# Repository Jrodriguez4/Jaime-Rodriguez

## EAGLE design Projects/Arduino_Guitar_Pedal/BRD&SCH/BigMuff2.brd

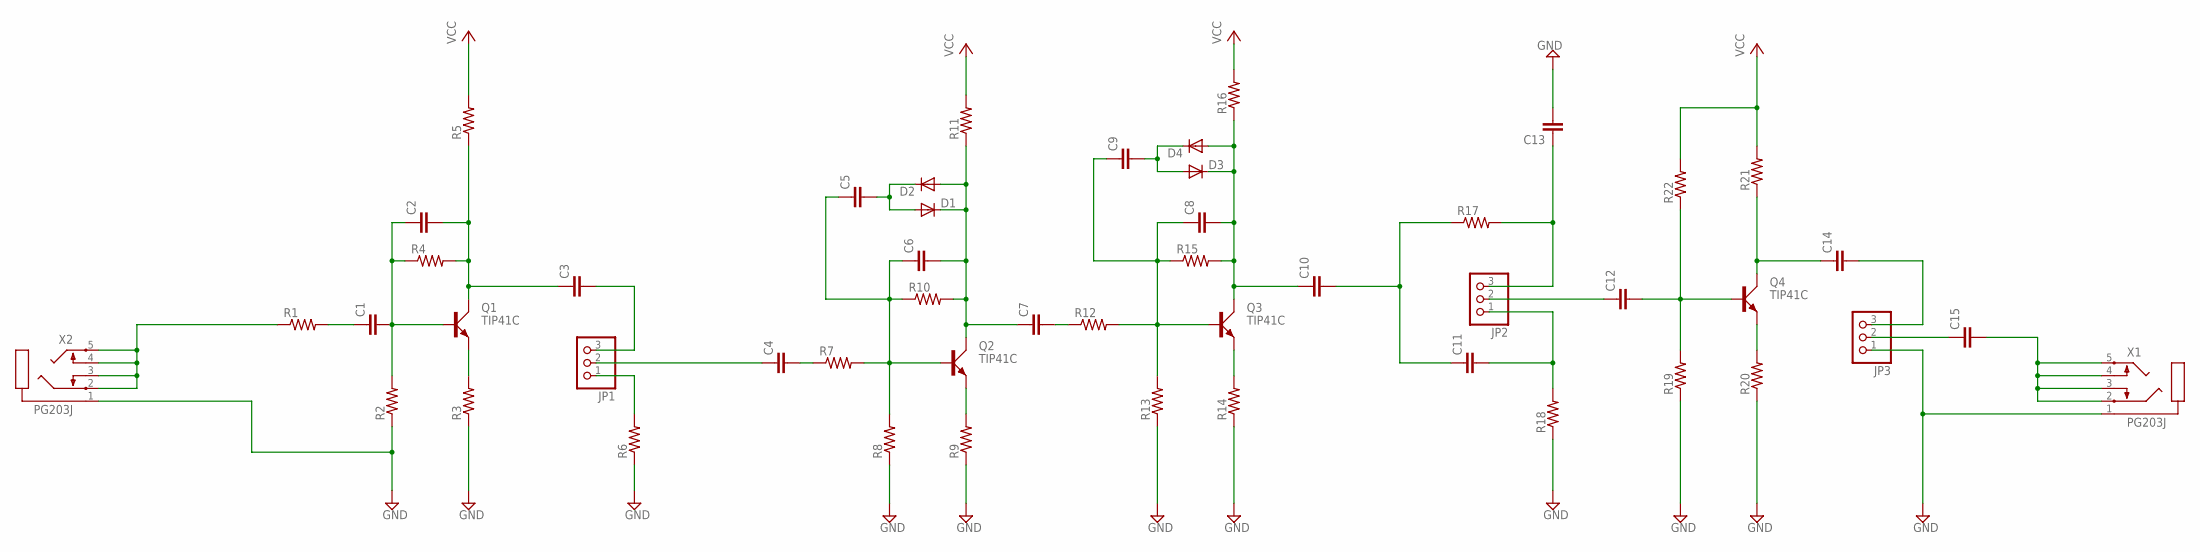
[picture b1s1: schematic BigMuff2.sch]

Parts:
C1, C2, C3, C4, C5, C6, C7, C8, C9, C10, C11, C12, C13, C14, C15: C2,5-3; C2.5-3
D1, D2, D3, D4: DIODE-D-2.5; D-2.5
JP1, JP2, JP3: PINHD-1X3; 1X03
Q1, Q2, Q3, Q4: TIP41C; TO220AV
R1, R2, R3, R4, R5, R6, R7, R8, R9, R10, R11, R12, R13, R14, R15, R16, R17, R18, R19, R20, R21, R22: R-US_0204/2V; 0204V
X1, X2: PG203J

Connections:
GND: C13.2, JP3.1, R2.1, R3.1, R6.1, R8.1, R9.1, R13.1, R14.1, R18.1, R19.1, R20.1, X1.1, X2.1; also elsewhere on the board
unnamed: C2.2, C3.1, Q1.C, R4.2, R5.1
unnamed: C1.2, C2.1, Q1.B, R2.2, R4.1
unnamed: C1.1, R1.2
unnamed: Q1.E, R3.2
unnamed: C3.2, JP1.3
unnamed: JP1.1, R6.2
unnamed: C14.1, Q4.C, R21.1
unnamed: C4.1, JP1.2
unnamed: C6.2, C7.1, D1.C, D2.A, Q2.C, R10.2, R11.1
unnamed: C5.2, D1.A, D2.C
unnamed: C5.1, C6.1, Q2.B, R7.2, R8.2, R10.1
unnamed: Q2.E, R9.2
unnamed: C7.2, R12.1
unnamed: C4.2, R7.1
unnamed: C15.2, X1.2, X1.3, X1.4, X1.5
unnamed: C8.2, C10.1, D3.C, D4.A, Q3.C, R15.2, R16.1
unnamed: C8.1, C9.1, Q3.B, R12.2, R13.2, R15.1
unnamed: Q3.E, R14.2
unnamed: C9.2, D3.A, D4.C
unnamed: C13.1, JP2.3, R17.2
unnamed: C10.2, C11.1, R17.1
unnamed: C12.1, JP2.2
unnamed: C12.2, Q4.B, R19.2, R22.1
unnamed: C11.2, JP2.1, R18.2
unnamed: Q4.E, R20.2
unnamed: C14.2, JP3.3
unnamed: R1.1, X2.2, X2.3, X2.4, X2.5
unnamed: C15.1, JP3.2
VCC: R5.2, R11.2, R16.2, R21.2, R22.2; also elsewhere on the board

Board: 2 copper layers, 52 parts (0 on the bottom side), 30 nets, no tracks yet.

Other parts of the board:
C16: C2.5-3
JP4: 1X03

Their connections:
GND: C16.1, JP4.1, JP4.2; also elsewhere on the board
VCC: C16.2, JP4.3; also elsewhere on the board

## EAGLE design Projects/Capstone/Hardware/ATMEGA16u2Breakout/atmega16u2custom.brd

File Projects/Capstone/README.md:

# Digital Dashboard

The digital dashboard project was completed by a group of students at Portland State University for the Electrical and Computer Engineering Capstone program on behalf of the Viking Motorsports team.

The digital dashboard is intended for a Formula SAE electric vehicle and functions as a visual display of information for various systems on the vehicle.

[Check out our wiki](https://github.com/noahterickson/DigitalDash/wiki)

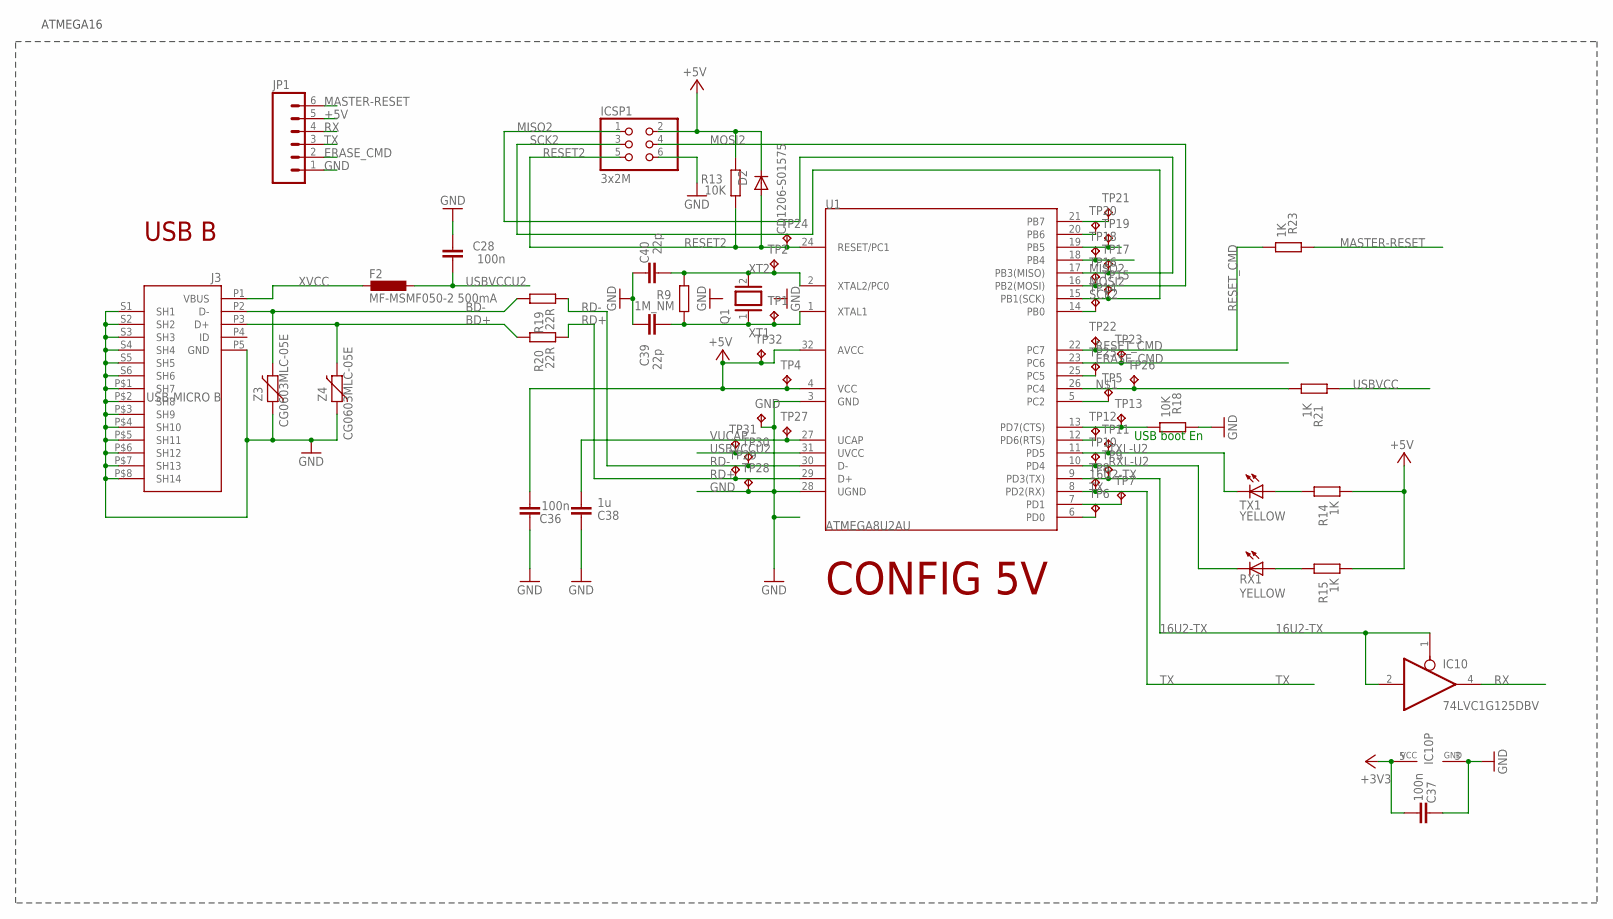
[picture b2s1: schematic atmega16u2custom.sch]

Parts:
C28, C36, C37: 100n; C0805
C38: 1u; C0805
C39, C40: 22p; C0805
D2: CD1206-S01575; MINIMELF
F2: MF-MSMF050-2 500mA; L1812
GND: TPB1,27; B1,27
IC10: 74LVC1G125DBV; SOT23-5
ICSP1: 3x2M; 2X03
J3: USB-MICRO B; CON2_USB_MICRO_B_AT
JP1: M06NO_SILK; 1X06_NO_SILK
Q1: XTAL/S; QS
R9: 1M_NM; R0805
R13, R18: 10K; R0805
R14, R15, R21, R23: 1K; R0805
R19, R20: 22R; R0805
RX1: YELLOW; CHIP-LED0805
TP1, TP2, TP4, TP5, TP6, TP7, TP8, TP9, TP10, TP11, TP12, TP13, TP14, TP15, TP16, TP17, TP18, TP19, TP20, TP21, TP22, TP23, TP24, TP25, TP26, TP27, TP28, TP29, TP30, TP31, TP32: TPB1,27; B1,27
TX1: YELLOW; CHIP-LED0805
U1: ATMEGA8U2AU; TQFP32-08
Z3, Z4: CG0603MLC-05E; CT/CN0603

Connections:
8PB4: TP18.TP, U1.18 (PB4)
8PB5: TP19.TP, U1.19 (PB5)
8PB6: TP20.TP, U1.20 (PB6)
16U2-TX: IC10.1 (OE), IC10.2 (I), TP9.TP, U1.9 (PD3(TX))
+3V3: C37.1, IC10.5 (VCC)
+5V: C36.1, D2.C, ICSP1.2, JP1.5, R13.2, R14.1, R15.1, TP4.TP, TP32.TP, U1.4 (VCC), U1.32 (AVCC)
BD+: J3.P3 (D+), R20.2, Z4.2
BD-: J3.P2 (D-), R19.2, Z3.2
DTR: R18.1, TP13.TP, U1.13 (PD7(CTS))
ERASE_CMD: JP1.2, TP23.TP, U1.23 (PC6)
GND: C28.2, C36.2, C37.2, C38.2, C39.2, C40.2, GND.TP, IC10.3 (GND), ICSP1.6, J3.P5 (GND), J3.P$1 (SH7), J3.P$2 (SH8), J3.P$3 (SH9), J3.P$4 (SH10), J3.P$5 (SH11), J3.P$6 (SH12), J3.P$7 (SH13), J3.P$8 (SH14), J3.S1 (SH1), J3.S2 (SH2), J3.S3 (SH3), J3.S4 (SH4), J3.S5 (SH5), J3.S6 (SH6), JP1.1, R18.2, TP28.TP, U1.3 (GND), U1.28 (UGND), Z3.1, Z4.1
MASTER-RESET: JP1.6, R23.2
MISO2: ICSP1.1, TP17.TP, U1.17 (PB3(MISO))
MOSI2: ICSP1.4, TP16.TP, U1.16 (PB2(MOSI))
unnamed: R21.1, TP26.TP, U1.26 (PC4)
unnamed: TP5.TP, U1.5 (PC2)
unnamed: TP6.TP, U1.6 (PD0)
unnamed: R15.2, RX1.A
unnamed: TP7.TP, U1.7 (PD1)
unnamed: TP12.TP, U1.12 (PD6(RTS))
unnamed: TP25.TP, U1.25 (PC5)
unnamed: TP14.TP, U1.14 (PB0)
unnamed: TP21.TP, U1.21 (PB7)
unnamed: R14.2, TX1.A
RD+: R20.1, TP29.TP, U1.29 (D+)
RD-: R19.1, TP30.TP, U1.30 (D-)
RESET2: D2.A, ICSP1.5, R13.1, TP24.TP, U1.24 (RESET/PC1)
RESET_CMD: R23.1, TP22.TP, U1.22 (PC7)
RX: IC10.4 (O), JP1.4
RXL-U2: RX1.C, TP10.TP, U1.10 (PD4)
SCK2: ICSP1.3, TP15.TP, U1.15 (PB1(SCK))
TX: JP1.3, TP8.TP, U1.8 (PD2(RX))
TXL-U2: TP11.TP, TX1.C, U1.11 (PD5)
USBVCC: R21.2
USBVCCU2: C28.1, F2.1, TP31.TP, U1.31 (UVCC)
VUCAP: C38.1, TP27.TP, U1.27 (UCAP)
XT1: C39.1, Q1.1, R9.1, TP1.TP, U1.1 (XTAL1)
XT2: C40.1, Q1.2, R9.2, TP2.TP, U1.2 (XTAL2/PC0)
XVCC: F2.2, J3.P1 (VBUS)

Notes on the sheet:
USB boot En
CONFIG 5V
USB B
ATMEGA16

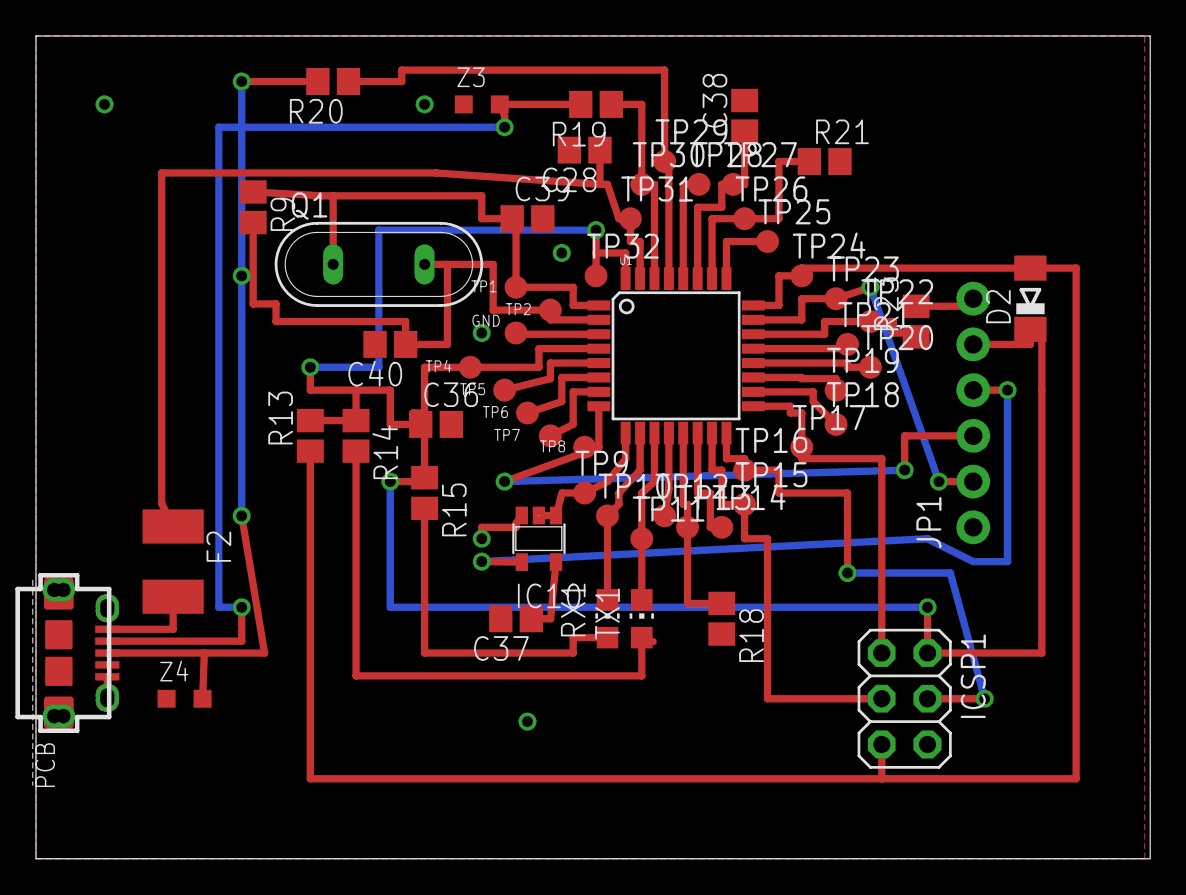
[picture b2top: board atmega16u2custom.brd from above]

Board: 2 copper layers, 61.9 x 45.7 mm, 59 parts (0 on the bottom side), 38 nets.

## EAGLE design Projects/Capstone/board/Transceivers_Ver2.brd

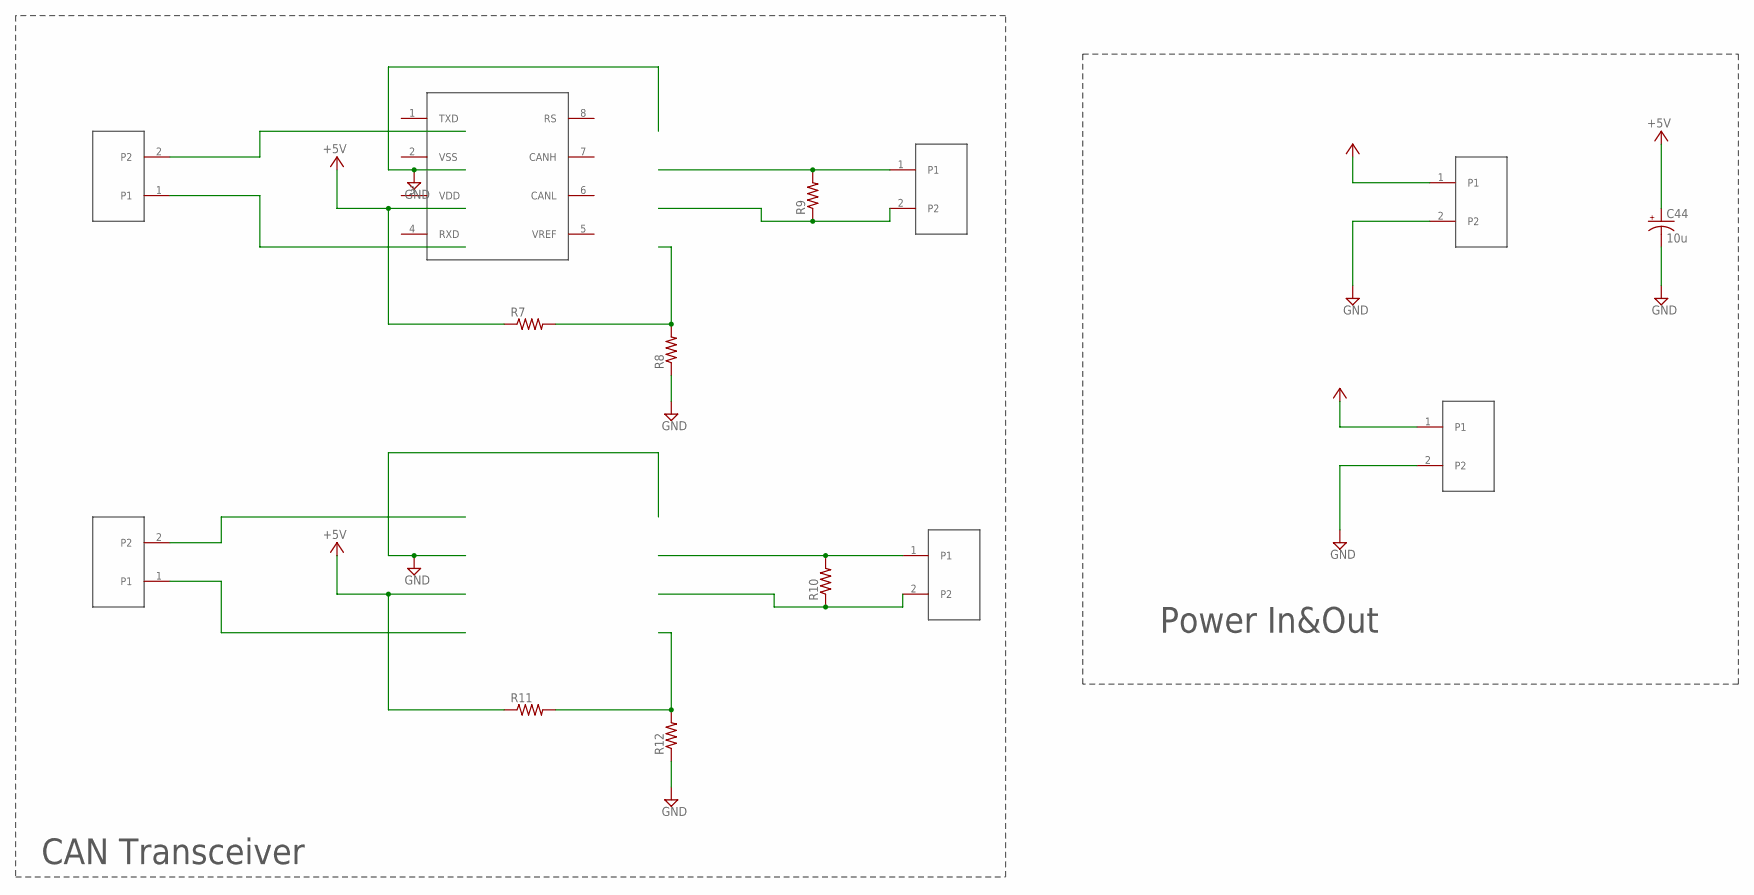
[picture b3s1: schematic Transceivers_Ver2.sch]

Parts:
C44: 10u; 153CLV-0405
CAN0, CAN1: CON-100MIL; 2X1-100MIL
POWER, POWER1: CON-100MIL; 2X1-100MIL
R7, R8, R9, R10, R11, R12: R-US_R0805; R0805
TXRX0, TXRX1: CON-100MIL; 2X1-100MIL
U$1: MCP2551-DIP; DIL08

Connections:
+5V: C44.+, POWER.1, POWER1.1, R7.1, R11.1
CH0: CAN0.1, R9.2
CH1: CAN1.1, R10.2
CL0: CAN0.2, R9.1
CL1: CAN1.2, R10.1
GND: C44.-, POWER.2, POWER1.2, R8.1, R12.1
unnamed: R7.2, R8.2
unnamed: R11.2, R12.2
RX0: TXRX0.1
RX1: TXRX1.1
TX0: TXRX0.2
TX1: TXRX1.2

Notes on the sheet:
CAN Transceiver
Power In&Out

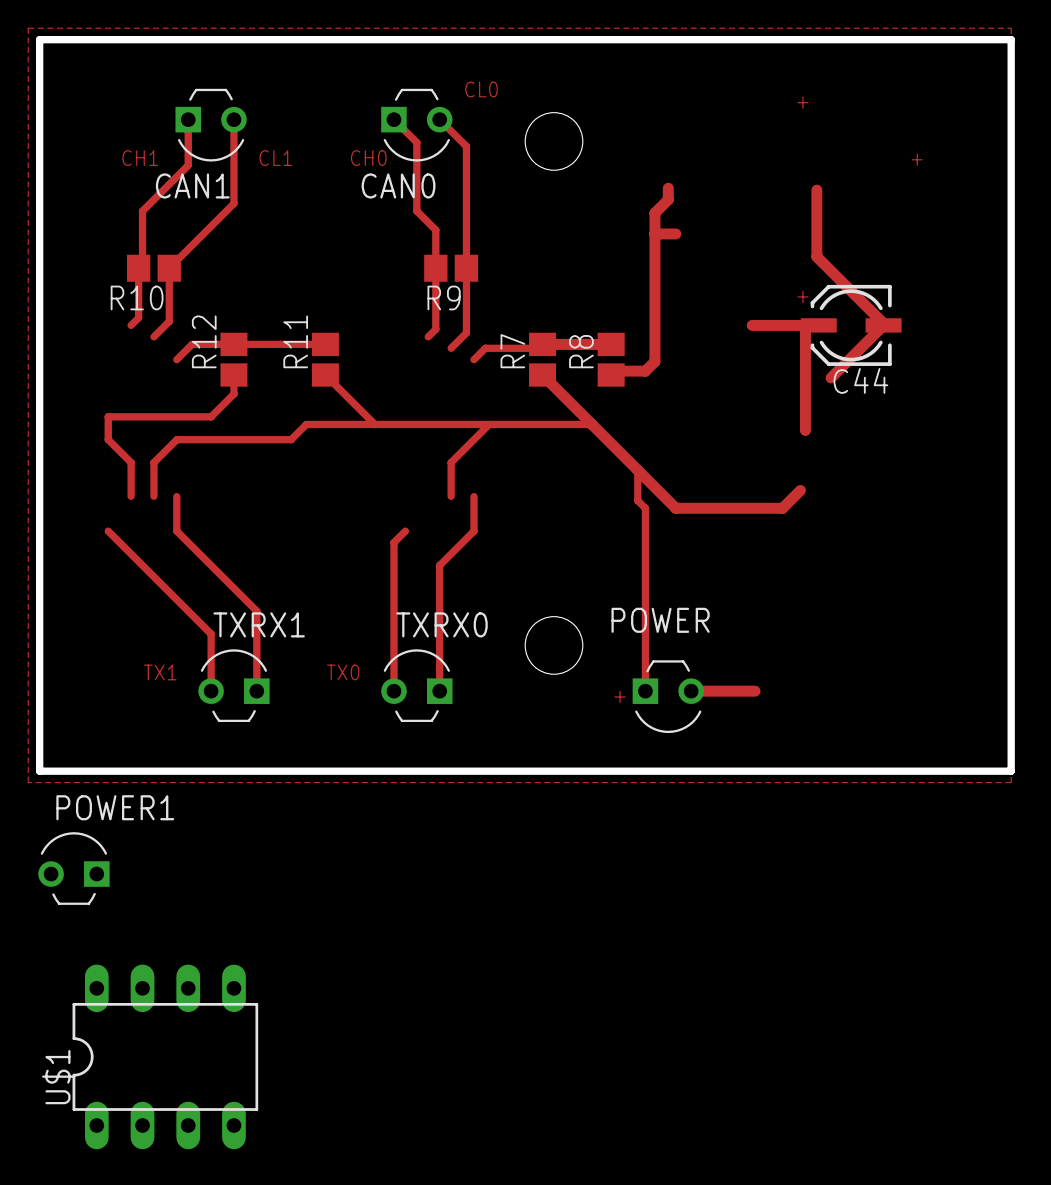
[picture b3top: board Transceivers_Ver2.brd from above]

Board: 2 copper layers, 54.0 x 40.6 mm, 14 parts (0 on the bottom side), 8 nets.

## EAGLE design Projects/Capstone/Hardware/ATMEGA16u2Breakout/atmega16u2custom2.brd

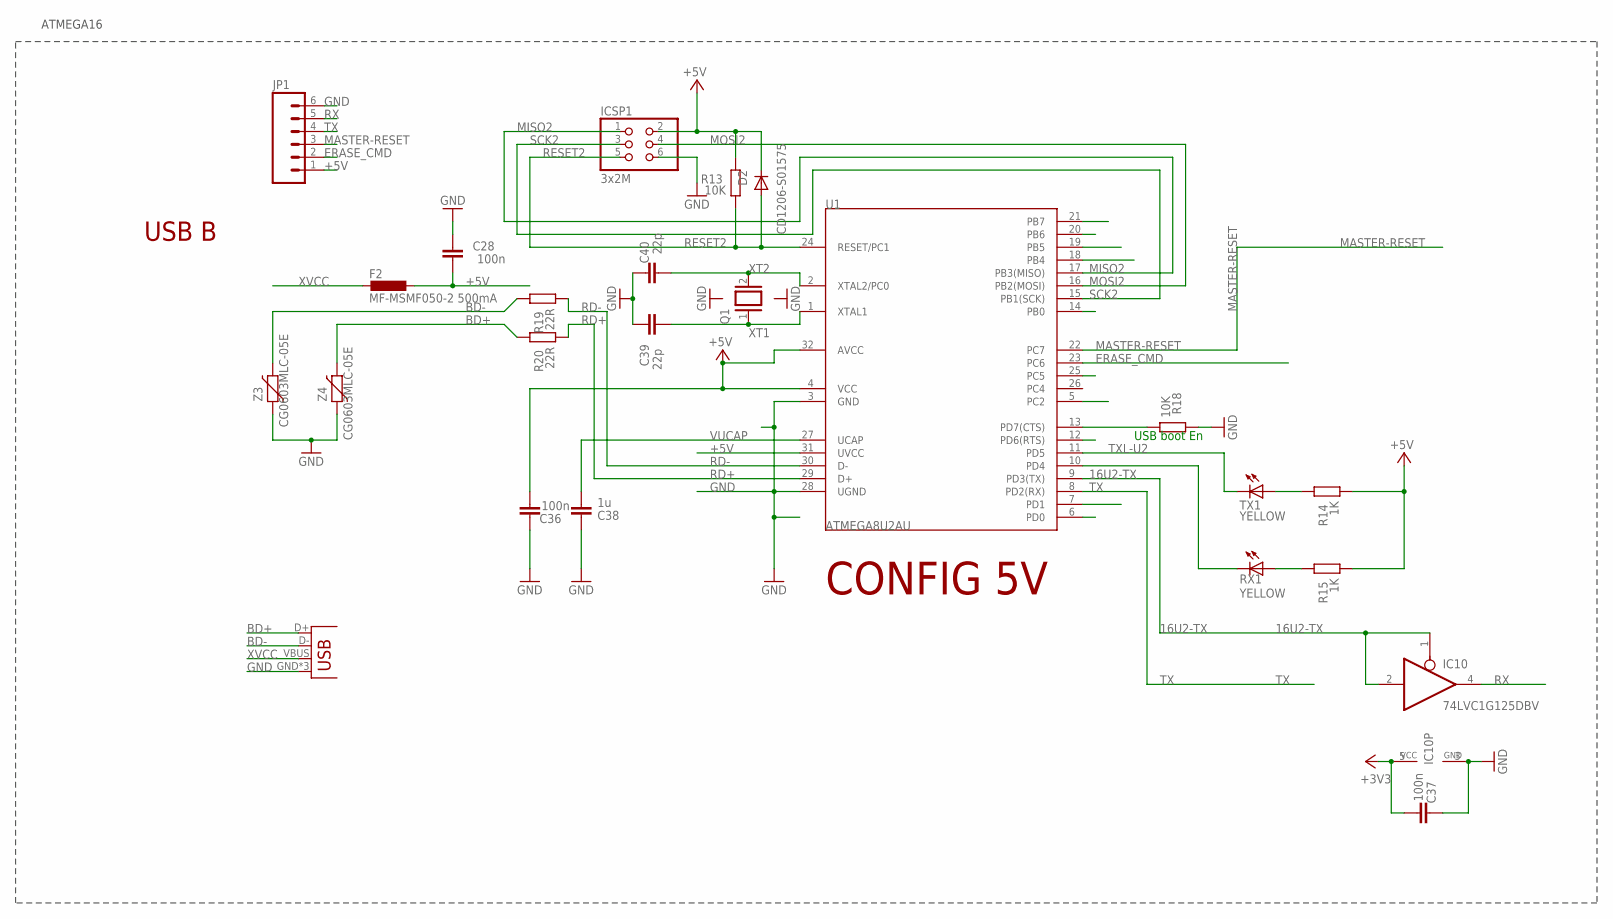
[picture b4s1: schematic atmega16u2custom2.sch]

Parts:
C28, C36, C37: 100n; C0805
C38: 1u; C0805
C39, C40: 22p; C0805
D2: CD1206-S01575; MINIMELF
F2: MF-MSMF050-2 500mA; L1812
IC10: 74LVC1G125DBV; SOT23-5
ICSP1: 3x2M; 2X03
JP1: M06NO_SILK; 1X06_NO_SILK
JP2: USB-MICROB
Q1: XTAL/S; QS
R13, R18: 10K; R0805
R14, R15: 1K; R0805
R19, R20: 22R; R0805
RX1: YELLOW; CHIP-LED0805
TX1: YELLOW; CHIP-LED0805
U1: ATMEGA8U2AU; TQFP32-08
Z3, Z4: CG0603MLC-05E; CT/CN0603

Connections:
8PB4: U1.18 (PB4)
8PB5: U1.19 (PB5)
8PB6: U1.20 (PB6)
16U2-TX: IC10.1 (OE), IC10.2 (I), U1.9 (PD3(TX))
+3V3: C37.1, IC10.5 (VCC)
+5V: C28.1, C36.1, D2.C, F2.1, ICSP1.2, JP1.1, R13.2, R14.1, R15.1, U1.4 (VCC), U1.31 (UVCC), U1.32 (AVCC)
BD+: JP2.D+, R20.2, Z4.2
BD-: JP2.D-, R19.2, Z3.2
DTR: R18.1, U1.13 (PD7(CTS))
ERASE_CMD: JP1.2, U1.23 (PC6)
GND: C28.2, C36.2, C37.2, C38.2, C39.2, C40.2, IC10.3 (GND), ICSP1.6, JP1.6, JP2.GND, JP2.MT1 (GND), JP2.MT2 (GND), R18.2, U1.3 (GND), U1.28 (UGND), Z3.1, Z4.1
MASTER-RESET: JP1.3, U1.22 (PC7)
MISO2: ICSP1.1, U1.17 (PB3(MISO))
MOSI2: ICSP1.4, U1.16 (PB2(MOSI))
unnamed: R15.2, RX1.A
unnamed: R14.2, TX1.A
RD+: R20.1, U1.29 (D+)
RD-: R19.1, U1.30 (D-)
RESET2: D2.A, ICSP1.5, R13.1, U1.24 (RESET/PC1)
RX: IC10.4 (O), JP1.5
RXL-U2: RX1.C, U1.10 (PD4)
SCK2: ICSP1.3, U1.15 (PB1(SCK))
TX: JP1.4, U1.8 (PD2(RX))
TXL-U2: TX1.C, U1.11 (PD5)
VUCAP: C38.1, U1.27 (UCAP)
XT1: C39.1, Q1.1, U1.1 (XTAL1)
XT2: C40.1, Q1.2, U1.2 (XTAL2/PC0)
XVCC: F2.2, JP2.VBUS

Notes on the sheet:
USB boot En
CONFIG 5V
USB B
ATMEGA16

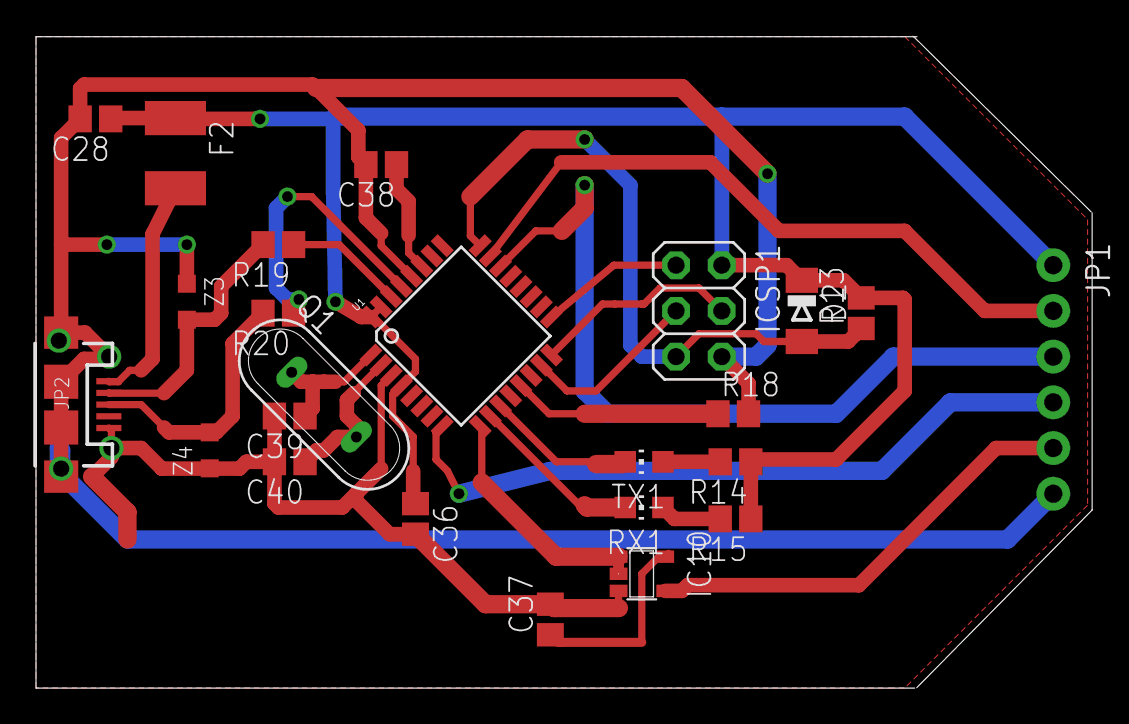
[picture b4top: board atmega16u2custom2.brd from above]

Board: 2 copper layers, 58.7 x 36.2 mm, 24 parts (0 on the bottom side), 25 nets.

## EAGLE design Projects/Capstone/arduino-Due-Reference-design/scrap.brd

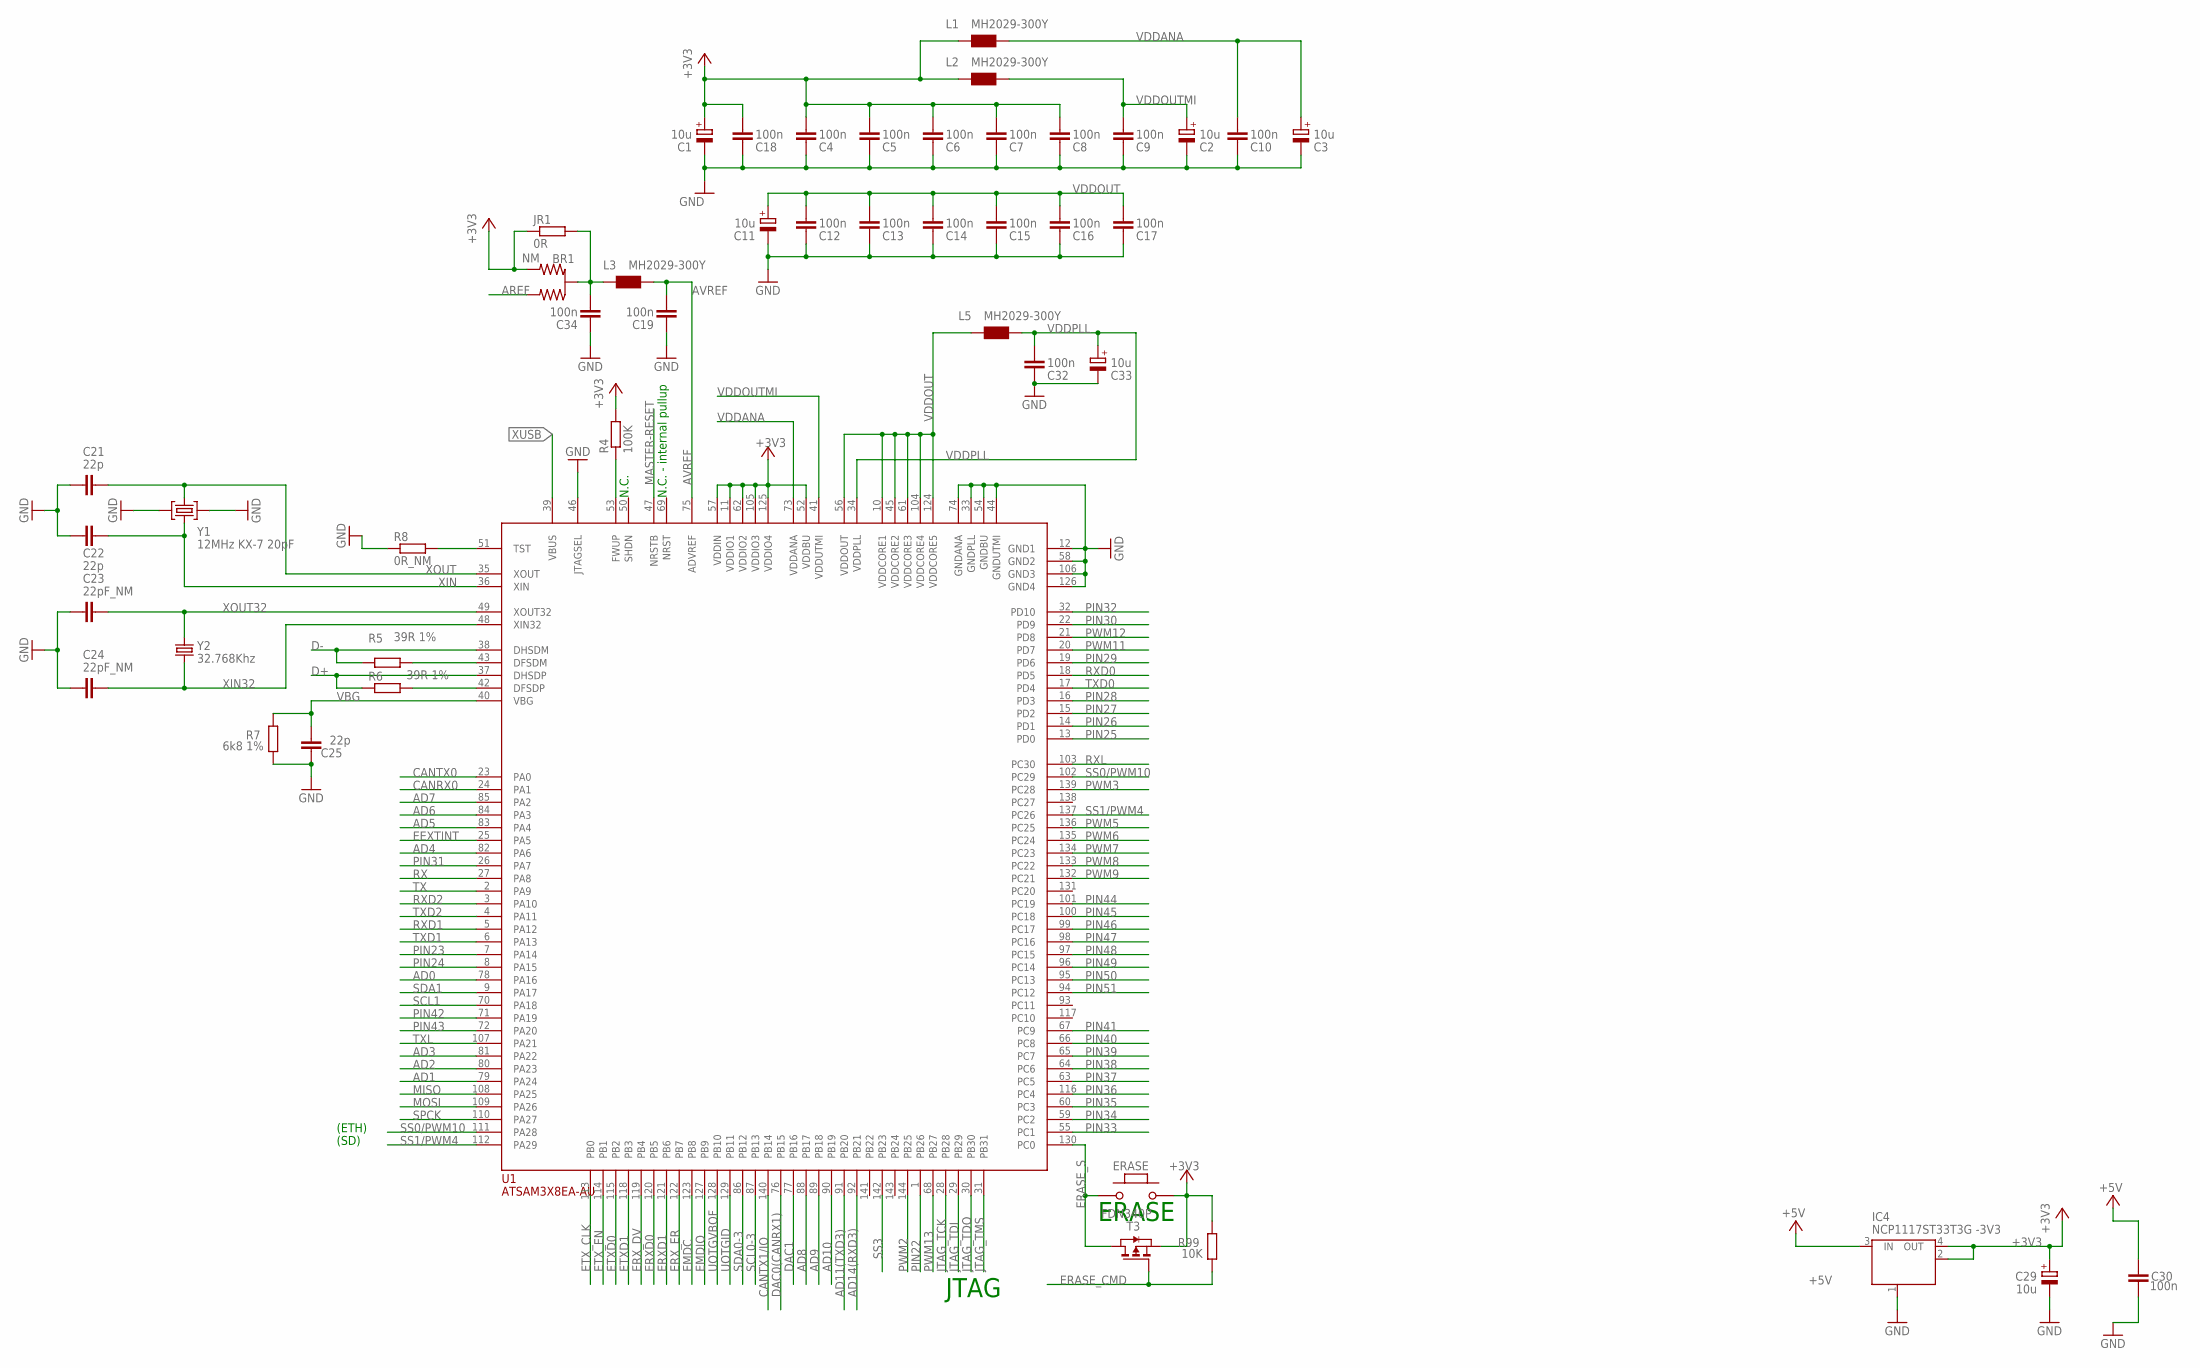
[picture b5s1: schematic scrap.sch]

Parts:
BR1: NM; J0402
C1, C2, C3, C11, C29, C33: 10u; SMC_B
C4, C5, C6, C7, C8, C9, C10, C12, C13, C14, C15, C16, C17, C18, C19, C30, C32, C34: 100n; C0402
C21, C22, C25: 22p; C0402
C23, C24: 22pF_NM; C0402
ERASE: MYSMD_PB157; SMD_157SW
IC4: NCP1117ST33T3G -3V3; SOT223
JR1: 0R; R0402
L1, L2, L3, L5: MH2029-300Y; 0805
R4: 100K; R0402
R5, R6: 39R 1%; R0402
R7: 6k8 1%; R0603-ROUND
R8: 0R_NM; R0402
R99: 10K; R0402
T3: FDN340P; SOT-23
U1: ATSAM3X8EA-AU; LQFP144
Y1: 12MHz KX-7 20pF; CRYSTAL-3.2-2.5
Y2: 32.768Khz; RESONATOR_EPSON_FC_145

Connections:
+3V3: BR1.3 (2), C1.+, C4.2, C5.2, C6.2, C7.2, C8.2, C18.2, C29.+, ERASE.1, IC4.2 (OUT), IC4.4 (OUT), JR1.1, L1.1, L2.1, R4.2, R99.2, T3.2 (S), U1.11 (VDDIO1), U1.52 (VDDBU), U1.57 (VDDIN), U1.62 (VDDIO2), U1.105 (VDDIO3), U1.125 (VDDIO4)
+5V: C30.2, IC4.3 (IN)
AD0: U1.78 (PA16)
AD1: U1.79 (PA24)
AD2: U1.80 (PA23)
AD3: U1.81 (PA22)
AD4: U1.82 (PA6)
AD5: U1.83 (PA4)
AD6: U1.84 (PA3)
AD7: U1.85 (PA2)
AD8: U1.88 (PB17)
AD9: U1.89 (PB18)
AD10: U1.90 (PB19)
AD11(TXD3): U1.91 (PB20)
AD14(RXD3): U1.92 (PB21)
AREF: BR1.1
AVREF: C19.2, L3.2, U1.75 (ADVREF)
AVREFL: BR1.2 (C), C34.2, JR1.2, L3.1
CANRX0: U1.24 (PA1)
CANTX0: U1.23 (PA0)
CANTX1/IO: U1.140 (PB14)
D+: R6.1, U1.37 (DHSDP)
D-: R5.1, U1.38 (DHSDM)
DAC0(CANRX1): U1.76 (PB15)
DAC1: U1.77 (PB16)
EEXTINT: U1.25 (PA5)
EMDC: U1.123 (PB8)
EMDIO: U1.127 (PB9)
ERASE_CMD: R99.1, T3.3 (G)
ERASE_S: ERASE.2, T3.1 (D), U1.130 (PC0)
ERXD0: U1.120 (PB5)
ERXD1: U1.121 (PB6)
ERX_DV: U1.119 (PB4)
ERX_ER: U1.122 (PB7)
ETXD0: U1.115 (PB2)
ETXD1: U1.118 (PB3)
ETX_CLK: U1.113 (PB0)
ETX_EN: U1.114 (PB1)
GND: C1.-, C2.-, C3.-, C4.1, C5.1, C6.1, C7.1, C8.1, C9.1, C10.1, C11.-, C12.1, C13.1, C14.1, C15.1, C16.1, C17.1, C18.1, C19.1, C21.2, C22.2, C23.2, C24.2, C25.2, C29.-, C30.1, C32.1, C33.-, C34.1, IC4.1 (GND/ADJ), R7.1, R8.1, U1.12 (GND1), U1.33 (GNDPLL), U1.44 (GNDUTMI), U1.46 (JTAGSEL), U1.54 (GNDBU), U1.58 (GND2), U1.74 (GNDANA), U1.106 (GND3), U1.126 (GND4), Y1.2 (GND), Y1.4 (GND)
JTAG_TCK: U1.28 (PB28)
JTAG_TDI: U1.29 (PB29)
JTAG_TDO: U1.30 (PB30)
JTAG_TMS: U1.31 (PB31)
MASTER-RESET: U1.47 (NRSTB)
MISO: U1.108 (PA25)
MOSI: U1.109 (PA26)
unnamed: R8.2, U1.51 (TST)
unnamed: R4.1, U1.53 (FWUP)
unnamed: R5.2, U1.43 (DFSDM)
unnamed: R6.2, U1.42 (DFSDP)
PIN22: U1.1 (PB26)
PIN23: U1.7 (PA14)
PIN24: U1.8 (PA15)
PIN25: U1.13 (PD0)
PIN26: U1.14 (PD1)
PIN27: U1.15 (PD2)
PIN28: U1.16 (PD3)
PIN29: U1.19 (PD6)
PIN30: U1.22 (PD9)
PIN31: U1.26 (PA7)
PIN32: U1.32 (PD10)
PIN33: U1.55 (PC1)
PIN34: U1.59 (PC2)
PIN35: U1.60 (PC3)
PIN36: U1.116 (PC4)
PIN37: U1.63 (PC5)
PIN38: U1.64 (PC6)
PIN39: U1.65 (PC7)
PIN40: U1.66 (PC8)
PIN41: U1.67 (PC9)
PIN42: U1.71 (PA19)
PIN43: U1.72 (PA20)
PIN44: U1.101 (PC19)
PIN45: U1.100 (PC18)
PIN46: U1.99 (PC17)
PIN47: U1.98 (PC16)
PIN48: U1.97 (PC15)
PIN49: U1.96 (PC14)
PIN50: U1.95 (PC13)
PIN51: U1.94 (PC12)
PWM2: U1.144 (PB25)
PWM3: U1.139 (PC28)
PWM5: U1.136 (PC25)
PWM6: U1.135 (PC24)
PWM7: U1.134 (PC23)
PWM8: U1.133 (PC22)
PWM9: U1.132 (PC21)
PWM11: U1.20 (PD7)
PWM12: U1.21 (PD8)
PWM13: U1.68 (PB27)
RX: U1.27 (PA8)
RXD0: U1.18 (PD5)
RXD1: U1.5 (PA12)
RXD2: U1.3 (PA10)
RXL: U1.103 (PC30)
SCL0-3: U1.87 (PB13)
SCL1: U1.70 (PA18)
SDA0-3: U1.86 (PB12)
SDA1: U1.9 (PA17)
SPCK: U1.110 (PA27)
SS0/PWM10: U1.102 (PC29), U1.111 (PA28)
SS1/PWM4: U1.112 (PA29), U1.137 (PC26)
SS3: U1.142 (PB23)
TX: U1.2 (PA9)
TXD0: U1.17 (PD4)
TXD1: U1.6 (PA13)
TXD2: U1.4 (PA11)
TXL: U1.107 (PA21)
UOTGID: U1.129 (PB11)
UOTGVBOF: U1.128 (PB10)
VBG: C25.1, R7.2, U1.40 (VBG)
VDDANA: C3.+, C10.2, L1.2, U1.73 (VDDANA)
VDDOUT: C11.+, C12.2, C13.2, C14.2, C15.2, C16.2, C17.2, L5.1, U1.10 (VDDCORE1), U1.45 (VDDCORE2), U1.56 (VDDOUT), U1.61 (VDDCORE3), U1.104 (VDDCORE4), U1.124 (VDDCORE5)
VDDOUTMI: C2.+, C9.2, L2.2, U1.41 (VDDUTMI)
VDDPLL: C32.2, C33.+, L5.2, U1.34 (VDDPLL)
XIN: C22.1, U1.36 (XIN), Y1.1 (C1)
XIN32: C24.1, U1.48 (XIN32), Y2.P$2 (2)
XOUT: C21.1, U1.35 (XOUT), Y1.3 (C2)
XOUT32: C23.1, U1.49 (XOUT32), Y2.P$1 (1)
XUSB: U1.39 (VBUS)

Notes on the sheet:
N.C.
JTAG
ERASE
(ETH)
(SD)
N.C. - internal pullup

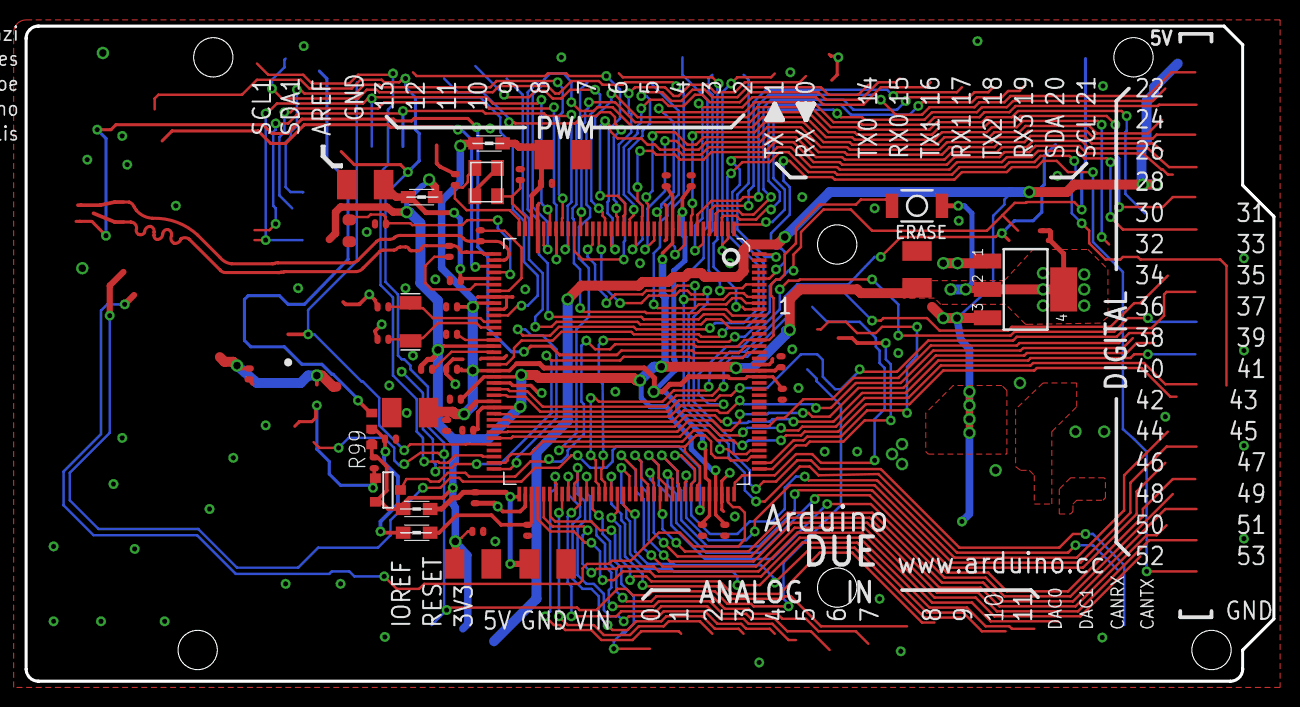
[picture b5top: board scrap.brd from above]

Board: 2 copper layers, 101.6 x 53.3 mm, 47 parts (0 on the bottom side), 24 nets.

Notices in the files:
parts and their libraries:
SparkFun-DigitalIC: Licensing: Creative Commons ShareAlike 4.0 International - https://creativecommons.org/licenses/by-sa/4.0
